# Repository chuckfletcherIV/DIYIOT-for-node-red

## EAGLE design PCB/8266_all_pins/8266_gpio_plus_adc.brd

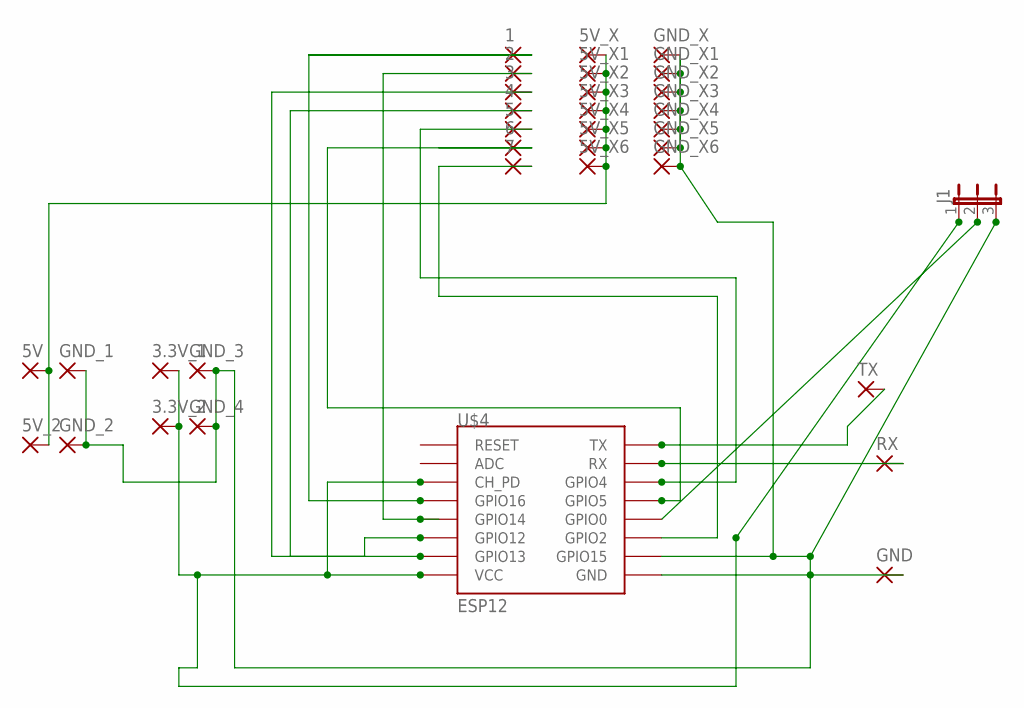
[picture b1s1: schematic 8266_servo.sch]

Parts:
1, 2, 3, 3.3V_1, 3.3V_2, 4, 5, 5V, 5V_2, 5V_X, 5V_X1, 5V_X2, 5V_X3, 5V_X4, 5V_X5, 5V_X6, 6, 7: 2,15/1,0
GND: 2,15/1,0
GND_1, GND_2, GND_3, GND_4: 2,15/1,0
GND_X, GND_X1, GND_X2, GND_X3, GND_X4, GND_X5, GND_X6: 2,15/1,0
J1: JP2E; JP2
RX: 2,15/1,0
TX: 2,15/1,0
U$4: ESP12

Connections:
5V: 5V.1, 5V_2.1, 5V_X.1, 5V_X1.1, 5V_X2.1, 5V_X3.1, 5V_X4.1, 5V_X5.1, 5V_X6.1; also elsewhere on the board
GND: GND.1, GND_1.1, GND_2.1, GND_3.1, GND_4.1, GND_X.1, GND_X1.1, GND_X2.1, GND_X3.1, GND_X4.1, GND_X5.1, GND_X6.1, J1.3, U$4.GND, U$4.GPIO15; also elsewhere on the board
unnamed: 2.1, U$4.GPIO14
unnamed: J1.2, U$4.GPIO0
unnamed: 3.1, U$4.GPIO12
unnamed: 4.1, U$4.GPIO13
unnamed: 3.3V_1.1, 3.3V_2.1, J1.1, U$4.CH_PD, U$4.VCC
unnamed: 1.1, U$4.GPIO16
unnamed: 7.1, U$4.GPIO2
unnamed: 6.1, U$4.GPIO5
unnamed: 5.1, U$4.GPIO4
unnamed 11: U$4.ADC; also elsewhere on the board
RX: RX.1, U$4.RX
TX: TX.1, U$4.TX

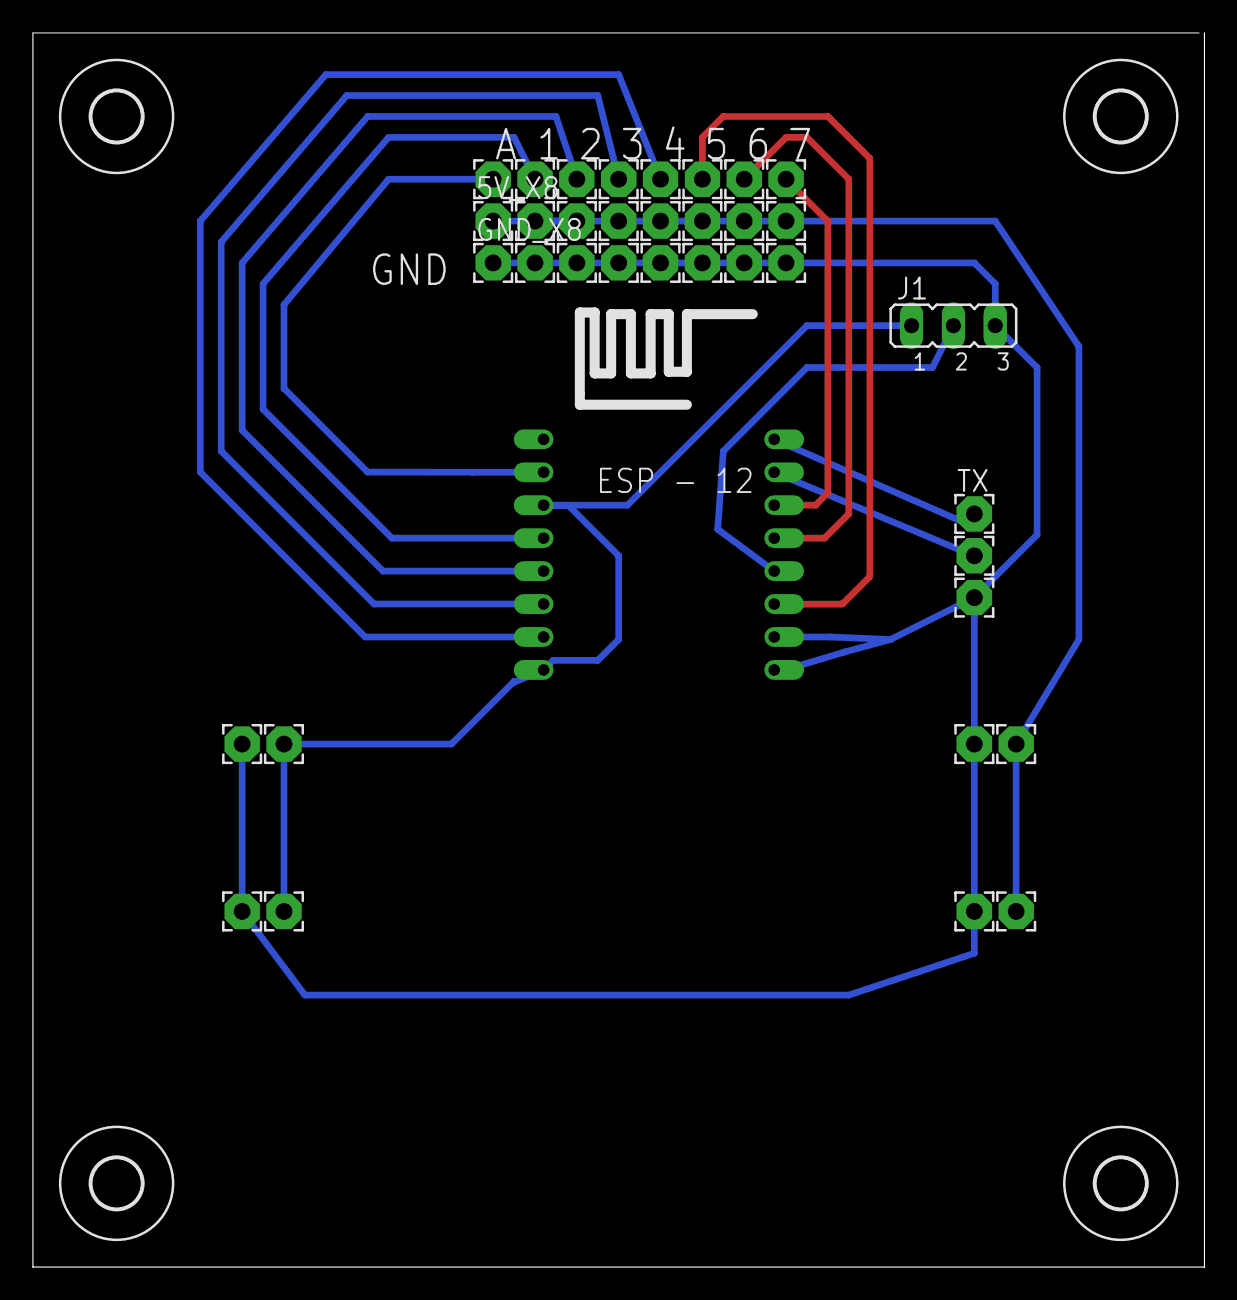
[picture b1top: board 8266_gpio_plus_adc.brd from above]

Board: 2 copper layers, 71.1 x 74.9 mm, 41 parts (0 on the bottom side), 14 nets.

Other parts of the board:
5V_X8: 2,15/1,0
ADC: 2,15/1,0
GND_X8: 2,15/1,0
U$1, U$2, U$5, U$6: 3,0

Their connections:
5V: 5V_X8.1; also elsewhere on the board
GND: GND_X8.1; also elsewhere on the board
unnamed 11: ADC.1; also elsewhere on the board

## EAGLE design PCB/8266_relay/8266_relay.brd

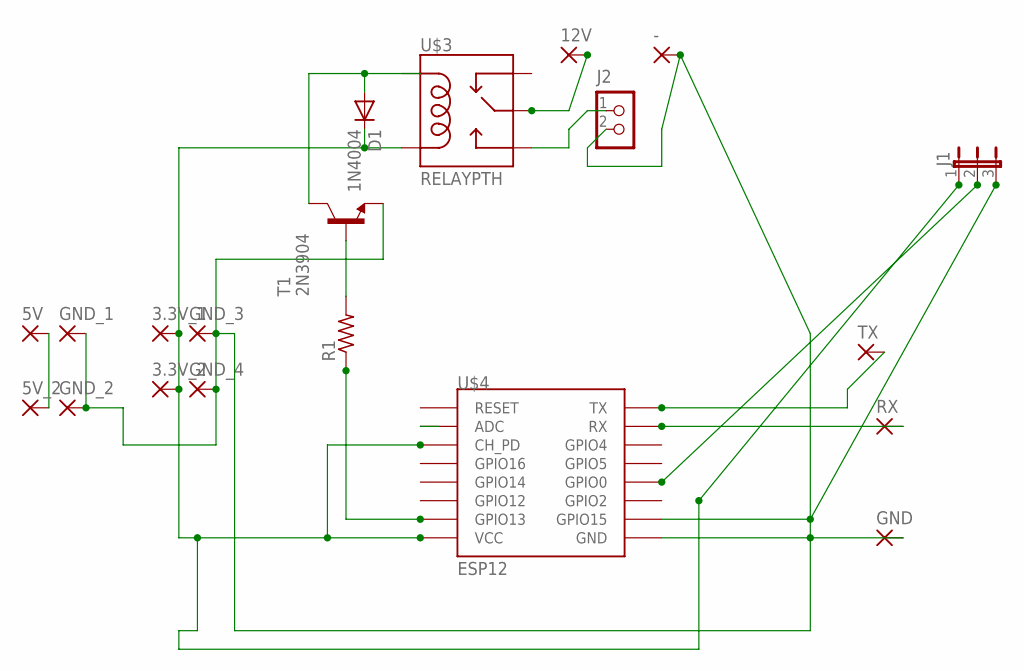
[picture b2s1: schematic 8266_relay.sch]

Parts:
3.3V_1, 3.3V_2, 5V, 5V_2, 12V: 2,15/1,0
-: 2,15/1,0
D1: 1N4004; DO41-10
GND: 2,15/1,0
GND_1, GND_2, GND_3, GND_4: 2,15/1,0
J1: JP2E; JP2
J2: CON_TERMINAL_BLOCK_02-5MM; TERMINAL_BLOCK_2P_5
R1: R-US_0309/10; 0309/10
RX: 2,15/1,0
T1: 2N3904; TO92
TX: 2,15/1,0
U$3: RELAYPTH; SRD-05VDC-SL-C
U$4: ESP12

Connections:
5V: 5V.1, 5V_2.1
12V: 12V.1, U$3.SWCOMMON
GND: -.1, GND.1, GND_1.1, GND_2.1, GND_3.1, GND_4.1, J1.3, J2.2, T1.3 (E), U$4.GND, U$4.GPIO15
unnamed: J1.2, U$4.GPIO0
unnamed: R1.1, U$4.GPIO13
unnamed: J2.1, U$3.SWOPEN
unnamed: 3.3V_1.1, 3.3V_2.1, D1.C, J1.1, U$3.COIL0, U$4.CH_PD, U$4.VCC
unnamed: D1.A, T1.1 (C), U$3.COIL1
unnamed: R1.2, T1.2 (B)
RX: RX.1, U$4.RX
TX: TX.1, U$4.TX

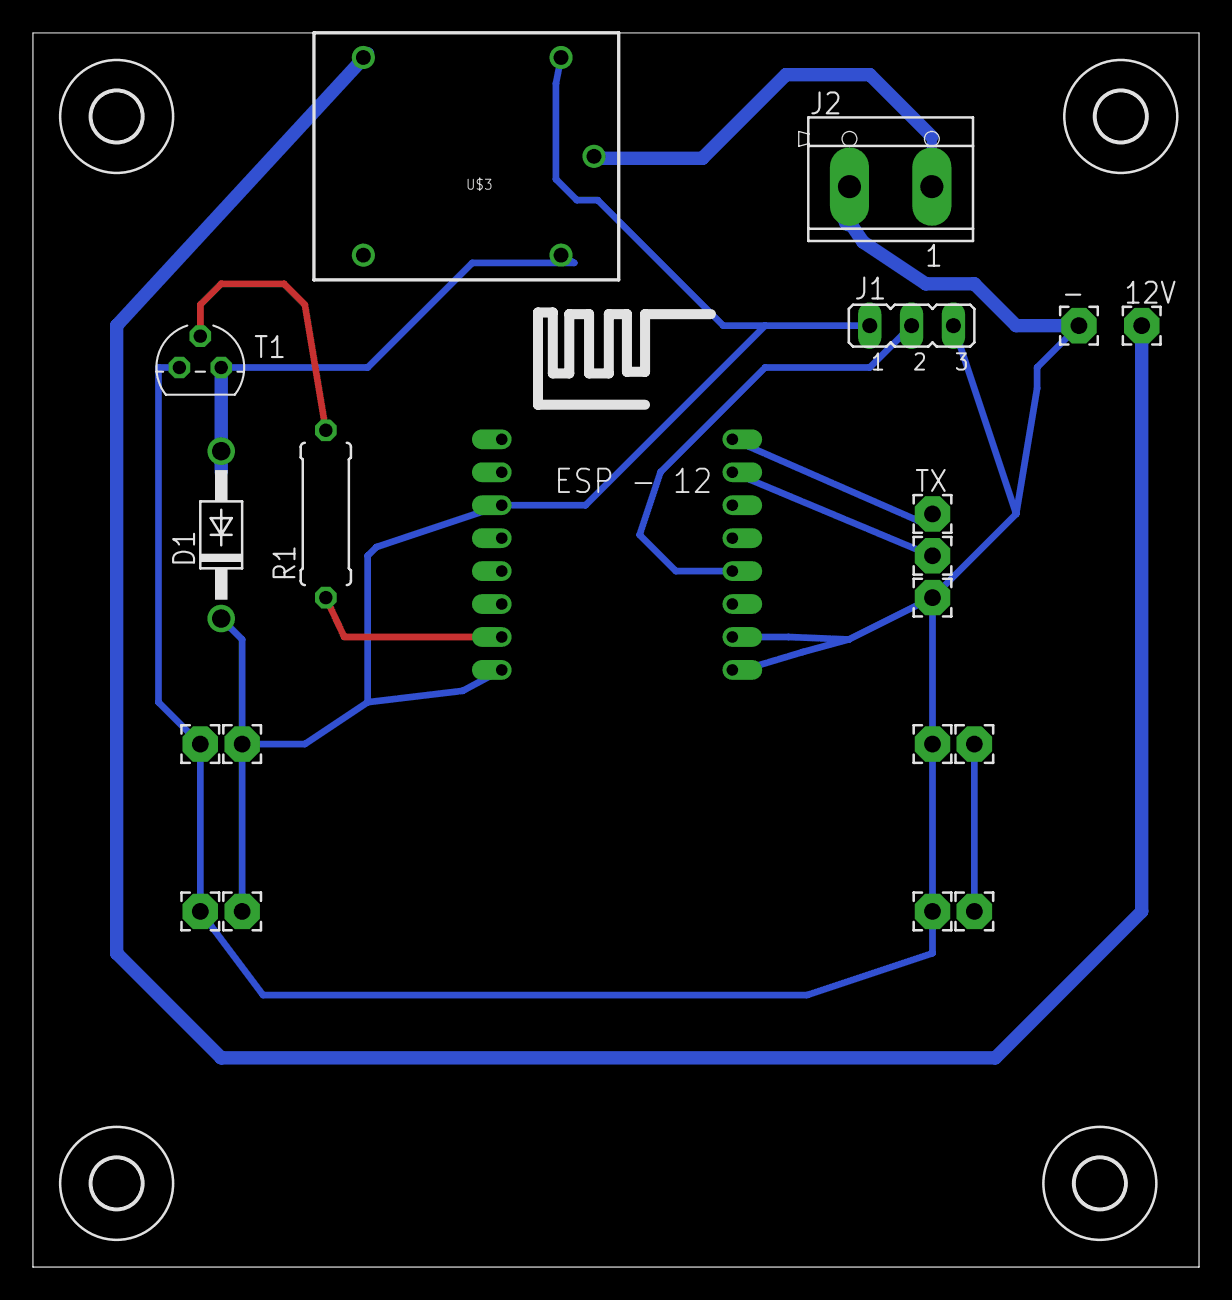
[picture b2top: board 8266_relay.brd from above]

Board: 2 copper layers, 70.8 x 74.9 mm, 24 parts (0 on the bottom side), 11 nets.

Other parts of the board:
U$1, U$2, U$5, U$6: 3,0
